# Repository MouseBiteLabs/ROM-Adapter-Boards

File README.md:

# ROM-Adapter-Boards
A collection of ROM adapter boards for different use cases

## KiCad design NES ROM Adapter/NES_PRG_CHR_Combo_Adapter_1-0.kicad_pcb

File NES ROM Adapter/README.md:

# NES ROM Adapter

Order at your own risk. Design is untested.

See instructions here: https://mousebitelabs.com/2020/06/17/eprom-to-nes-mask-rom-adapter-board/

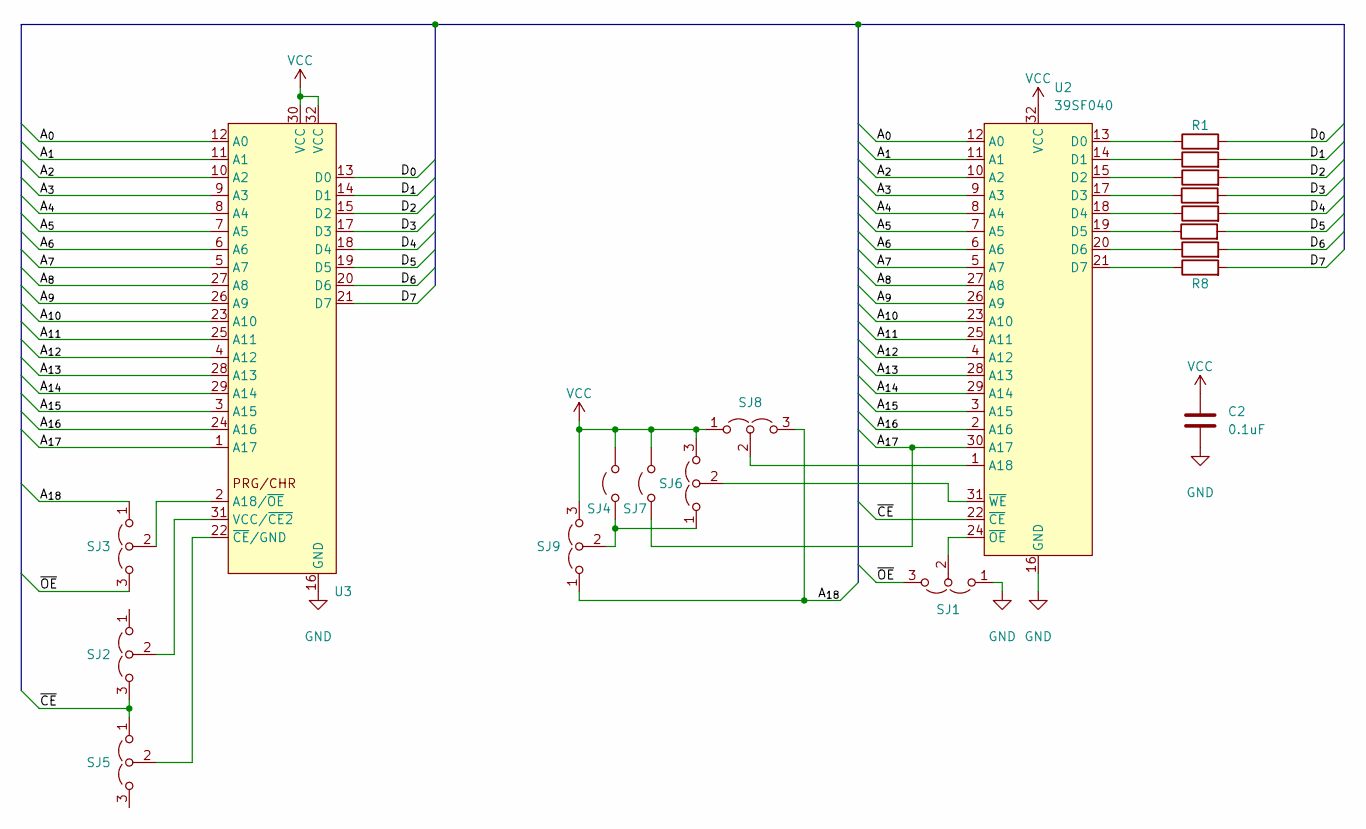
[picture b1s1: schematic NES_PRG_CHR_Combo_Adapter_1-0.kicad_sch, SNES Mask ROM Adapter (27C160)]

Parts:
C2: 0.1uF; THT_SMT_0803
R1, R2, R3, R4, R5, R6, R7, R8: R; R_0603_1608Metric_Boxed_SHORTED_DASHED
SJ1, SJ2, SJ3, SJ5, SJ6, SJ8, SJ9: Jumper_3_Open; SJ_2
SJ4, SJ7: Jumper_2_Open; SJ
U2, U3: 39SF040; DIP-32_W15.24mm

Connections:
/A_{0}: U2.12 (A0), U3.12 (A0); also elsewhere on the board
/A_{1}: U2.11 (A1), U3.11 (A1); also elsewhere on the board
/A_{2}: U2.10 (A2), U3.10 (A2); also elsewhere on the board
/A_{3}: U2.9 (A3), U3.9 (A3); also elsewhere on the board
/A_{4}: U2.8 (A4), U3.8 (A4); also elsewhere on the board
/A_{5}: U2.7 (A5), U3.7 (A5); also elsewhere on the board
/A_{6}: U2.6 (A6), U3.6 (A6); also elsewhere on the board
/A_{7}: U2.5 (A7), U3.5 (A7); also elsewhere on the board
/A_{8}: U2.27 (A8), U3.27 (A8); also elsewhere on the board
/A_{9}: U2.26 (A9), U3.26 (A9); also elsewhere on the board
/A_{10}: U2.23 (A10), U3.23 (A10); also elsewhere on the board
/A_{11}: U2.25 (A11), U3.25 (A11); also elsewhere on the board
/A_{12}: U2.4 (A12), U3.4 (A12); also elsewhere on the board
/A_{13}: U2.28 (A13), U3.28 (A13); also elsewhere on the board
/A_{14}: U2.29 (A14), U3.29 (A14); also elsewhere on the board
/A_{15}: U2.3 (A15), U3.3 (A15); also elsewhere on the board
/A_{16}: U2.2 (A16), U3.24 (A16); also elsewhere on the board
/A_{17}: SJ7.1 (A), U2.30 (A17), U3.1 (A17); also elsewhere on the board
/A_{18}: SJ3.1 (A), SJ8.3 (B), SJ9.1 (A)
/D_{0}: R1.2, U3.13 (D0)
/D_{1}: R2.2, U3.14 (D1)
/D_{2}: R3.2, U3.15 (D2)
/D_{3}: R4.2, U3.17 (D3)
/D_{4}: R5.2, U3.18 (D4)
/D_{5}: R6.2, U3.19 (D5)
/D_{6}: R7.2, U3.20 (D6)
/D_{7}: R8.2, U3.21 (D7)
/~CE: SJ2.3 (B), SJ5.1 (A), U2.22 (~CE); also elsewhere on the board
/~OE: SJ1.3 (B), SJ3.3 (B)
GND: C2.2, SJ1.1 (A), U2.16 (GND), U3.16 (GND); also elsewhere on the board
unnamed 30: SJ1.2 (C), U2.24 (~OE); also elsewhere on the board
unnamed: SJ2.2 (C), U3.31 (VCC/~CE2)
unnamed: SJ3.2 (C), U3.2 (A18/~OE)
unnamed: SJ4.1 (A), SJ6.1 (A), SJ9.2 (C)
unnamed: SJ5.2 (C), U3.22 (~CE/GND)
unnamed 35: SJ6.2 (C), U2.31 (~WE); also elsewhere on the board
unnamed 36: SJ8.2 (C), U2.1 (A18); also elsewhere on the board
unnamed 37: R1.1, U2.13 (D0); also elsewhere on the board
unnamed 38: R2.1, U2.14 (D1); also elsewhere on the board
unnamed 39: R3.1, U2.15 (D2); also elsewhere on the board
unnamed 40: R4.1, U2.17 (D3); also elsewhere on the board
unnamed 41: R5.1, U2.18 (D4); also elsewhere on the board
unnamed 42: R6.1, U2.19 (D5); also elsewhere on the board
unnamed 43: R7.1, U2.20 (D6); also elsewhere on the board
unnamed 44: R8.1, U2.21 (D7); also elsewhere on the board
VCC: C2.1, SJ4.2 (B), SJ6.3 (B), SJ7.2 (B), SJ8.1 (A), SJ9.3 (B), U2.32 (VCC), U3.30 (VCC), U3.32 (VCC); also elsewhere on the board

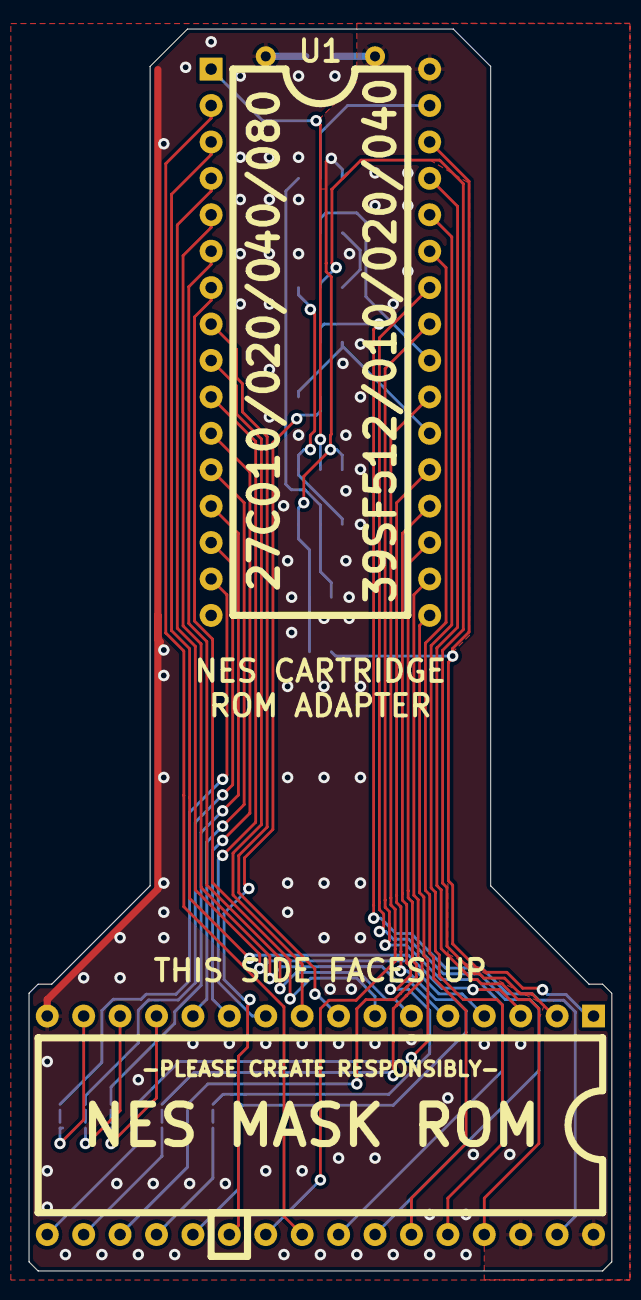
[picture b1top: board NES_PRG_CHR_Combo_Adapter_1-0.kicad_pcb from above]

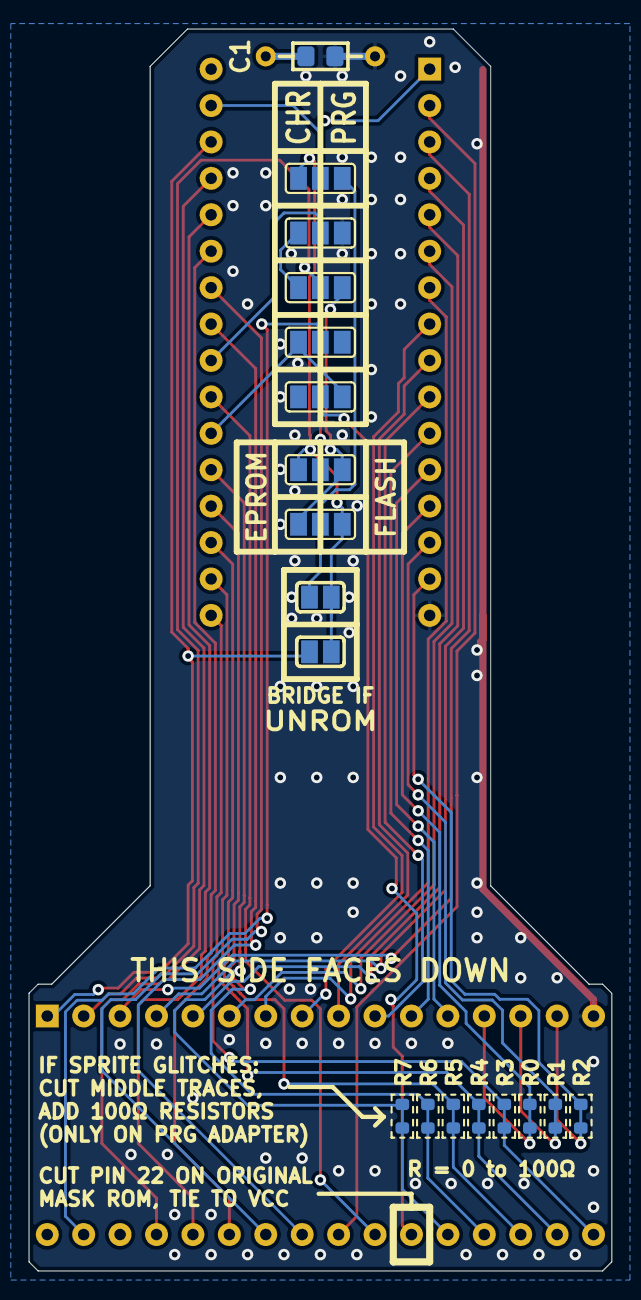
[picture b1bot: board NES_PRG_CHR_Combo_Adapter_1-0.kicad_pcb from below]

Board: 2 copper layers, 40.6 x 86.6 mm, 20 parts (18 on the bottom side), 46 nets.

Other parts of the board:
C1: 0.1uF; THT_SMT_0803
U1: 39SF040; DIP-32_W15.24mm

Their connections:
/A_{0}: U1.12 (A0); also elsewhere on the board
/A_{1}: U1.11 (A1); also elsewhere on the board
/A_{2}: U1.10 (A2); also elsewhere on the board
/A_{3}: U1.9 (A3); also elsewhere on the board
/A_{4}: U1.8 (A4); also elsewhere on the board
/A_{5}: U1.7 (A5); also elsewhere on the board
/A_{6}: U1.6 (A6); also elsewhere on the board
/A_{7}: U1.5 (A7); also elsewhere on the board
/A_{8}: U1.27 (A8); also elsewhere on the board
/A_{9}: U1.26 (A9); also elsewhere on the board
/A_{10}: U1.23 (A10); also elsewhere on the board
/A_{11}: U1.25 (A11); also elsewhere on the board
/A_{12}: U1.4 (A12); also elsewhere on the board
/A_{13}: U1.28 (A13); also elsewhere on the board
/A_{14}: U1.29 (A14); also elsewhere on the board
/A_{15}: U1.3 (A15); also elsewhere on the board
/A_{16}: U1.2 (A16); also elsewhere on the board
/A_{17}: U1.30 (A17); also elsewhere on the board
/~CE: U1.22 (~CE); also elsewhere on the board
GND: C1.2, U1.16 (GND); also elsewhere on the board
unnamed 30: U1.24 (~OE); also elsewhere on the board
unnamed 35: U1.31 (~WE); also elsewhere on the board
unnamed 36: U1.1 (A18); also elsewhere on the board
unnamed 37: U1.13 (D0); also elsewhere on the board
unnamed 38: U1.14 (D1); also elsewhere on the board
unnamed 39: U1.15 (D2); also elsewhere on the board
unnamed 40: U1.17 (D3); also elsewhere on the board
unnamed 41: U1.18 (D4); also elsewhere on the board
unnamed 42: U1.19 (D5); also elsewhere on the board
unnamed 43: U1.20 (D6); also elsewhere on the board
unnamed 44: U1.21 (D7); also elsewhere on the board
VCC: C1.1, U1.32 (VCC); also elsewhere on the board

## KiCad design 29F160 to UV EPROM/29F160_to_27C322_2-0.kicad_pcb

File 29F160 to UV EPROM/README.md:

# 29F160 to UV ERPOM Adapter

This board is used to recreate the old UV EPROMs 27C160 and 27C322 with brand new 29F160 EEPROMs. The UV EPROMs are typically only available to purchase used from places like AliExpress and eBay, and are known to occasionally arrive damaged or completely inoperable. The 29F160, however, is brand new NOR Flash manufactured by Alliance, for purchase at major electronics distributors.

<a href="https://mou.sr/3HIjb09">Here is a link to the component on Mouser.</a>

With one of these chips, you can make a replacement for the 27C160. With two, you can make a replacement for the 27C322. In fact, with the 29F160's /BYTE pin, you can even make an 8-bit bus version of the 27C322 which was only ever a feature of the 27C160.

*(In this image, the board is set up as a drop-in replacement for the 27C322)*

All gerbers and source files can be found in this repo, as this project is fully open source. Please read all instructions associated with this board before assembling.

## Board Characteristics and Order Information

The zipped folder contains all the gerber files for this board. You can generally choose whatever thickness you want, but I usually stick to at least 1.0mm. The surface finish can also be whatever you want, but I find ENIG easier to solder the small-pitch parts, personally. Also note that this is a four-layer board.

You can order this board on OSH Park, which is a great option if you only need a small quantity: [https://oshpark.com/shared_projects/efulo1p1](https://oshpark.com/shared_projects/efulo1p1)

Alternatively, you can use the zipped folder at any board fabricator you like. You may also buy the board from PCBWay using this link (NOT YET AVAILABLE) (disclosure: I receive 10% of the sale value to go towards future PCB orders of my own):

## Required Equipment

- You will need basic tools, like a soldering iron, hot plate, and/or hot air rework station. Drag soldering will be indispensible for this board.
- To program the 29F160 chips, you can use the <a href="https://xgecu.myshopify.com/products/xgecu-new-t48-tl866-3gprogrammer-v12-01-support-28000-ics-for-spi-nor-nand-flash-emmc-bga153-162-169-100-221-tsop-sop-plcc">T48 programmer</a> with the <a href="https://xgecu.myshopify.com/products/100-original-xgecu-adp_f48_ex-1-tsop48-special-adapter-for-nor-flash-only-use-on-t48-tl866-3g-programmer">TSOP48 adapter</a>.

## Programming Adapter

To make programming this board easier, I made this mouthful of an adapter board: the <a href="https://github.com/MouseBiteLabs/TSOP-NOR-Flash-Programming-Adapter-for-T48">TSOP NOR Flash Programming Adapter for T48</a>. It is untested (I haven't received them yet) but if it works, it will let you program both of the 29F160 chips on this breakout board without having to desolder them. You **will still need** the <a href="https://xgecu.myshopify.com/products/100-original-xgecu-adp_f48_ex-1-tsop48-special-adapter-for-nor-flash-only-use-on-t48-tl866-3g-programmer">TSOP48 adapter</a> because there's a proprietary EEPROM chip on there to communicate with the main programmer, but this makes it easier nonetheless.

Remember: this adapter is untested. I will update this repository after testing it.

## Board Configurations

Most of the configurations are self-explanatory or are described on the back of the board, but here's a breakdown.

### JP1 - 27C160 Mode Jumper

Bridge this solder pad if you are only using one 29F160 chip to replicate a 27C160. Note that this pad is located underneath U4 - meaning you **should not solder JP1 if you have U4 on the board**. U4 is required if you are using two 29F160 chips.

### R2 - The Byte Mode Resistor

This is a special three-way set of pads that sets the mode for the databus output. These sets of pads configures the 29F160's /BYTE pin, which tells the chip to output data in an 8-bit bus or a 16-bit bus. The 27C160 had the same pin feature (as pin 32) but the 27C322 was forced to output a 16-bit bus. The /BYTE pin(s) on U2 and U3 are connected to the middle-right pad. Solder a resistor between the top or bottom set of pads, or directly connect this pad to the left (labeled "P32") according to the following criteria:

- Solder the resistor R2 to the bottom footprint to force the data output to be a 16-bit bus. This is how the 27C322 operates natively, and one of the modes the 27C160 can operate in. If you are using two 29F160 chips, then soldering to the bottom pad will produce a drop-in replacement for the 27C322.
- Solder the resistor R2 to the top footprint to force the data output to be an 8-bit bus. The 27C160 can output an 8-bit bus, but the 27C322 was never able to!
- Directly solder to the left (or use a zero-ohm resistor) to replicate the 27C160 as a drop-in replacement. This is ONLY if you are replicating the 27C160, NOT the 27C322. Soldering to the left will connect the 29F160's /BYTE pin to the through-hole pin 32, which is where the 27C160's /BYTE pin is located. **Do not solder to the left if you are using two 29F160 chips! Pin 32 in this case is the top address pin for switching between the two chips, so it is already in use!**

NOTE: Instead of a solder blob for P32 connection, a zero-ohm resistor may be used instead. **Do not use any resistance value other than zero ohms for R2 if connecting to P32.**

## The /WE, /RP, and /BYTE Holes

R1 and R3 are pull-up resistors for /WE and /RP pins on the 29F160s. When in normal operation, these two pins need to be pulled to VCC to operate properly. The /BYTE pin, as described in the section above, needs to be pulled to VCC or GND through R2 (or controlled through pin 32 elsewhere on the main board this is connecting to). The /BYTE pin is connected to the hole on the right side, also labeled /BYTE.

These holes are for easy access for potential on-board programming (these are used by the aformentioned <a href="https://github.com/MouseBiteLabs/29F160-to-UV-EPROM-T48-Programming-Adapter/">29F160 to UV EPROM Programmming Adapter for the T48</a>). If you are using this adapter board on one of my cartridges, there may be support for in-circuit programming through these pins. See the repository for the cartridge in question for more information.

## Bill of Materials (BOM): 27C160 (16 Mbit or 2 MB)

| Reference | Value/Part Number | Package | Description      | Source                                           |
| --------- | ----------------- | ------- | ---------------- | ------------------------------------------------ |
| C1        | 0.1uF             | 0603    | Capacitor (MLCC) | [https://mou.sr/3ENc15O](https://mou.sr/3ENc15O) |
| R1        | 100k              | 0603    | Resistor         | https://mou.sr/49bgMnu                           |
| R2 (*NOTE)| 100k              | 0603    | Resistor         | https://mou.sr/49bgMnu                           |
| R2 (*NOTE)| Zero ohms         | 0603    | Resistor (Jumper)| https://mou.sr/4e1ABQg                           |
| R3        | 100k              | 0603    | Resistor         | https://mou.sr/49bgMnu                           |
| U2        | M29F160           | TSOP-48 | Flash EEPROM     | https://mou.sr/3HIjb09                           |

NOTE: As described above, R2 is zero ohms (or a short circuit) to the P32 pad if you are using this board as a drop-in replacement for 27C160.

## Bill of Materials (BOM): 27C322 (32 Mbit or 4 MB)

| Reference | Value/Part Number | Package  | Description      | Source                                           |
| --------- | ----------------- | -------- | ---------------- | ------------------------------------------------ |
| C1        | 0.1uF             | 0603     | Capacitor (MLCC) | [https://mou.sr/3ENc15O](https://mou.sr/3ENc15O) |
| C2        | 0.1uF             | 0603     | Capacitor (MLCC) | [https://mou.sr/3ENc15O](https://mou.sr/3ENc15O) |
| R1        | 100k              | 0603     | Resistor         | https://mou.sr/49bgMnu                           |
| R2        | 100k              | 0603     | Resistor         | https://mou.sr/49bgMnu                           |
| R3        | 100k              | 0603     | Resistor         | https://mou.sr/49bgMnu                           |
| U2        | M29F160           | TSOP-48  | Flash EEPROM     | https://mou.sr/3HIjb09                           |
| U3        | M29F160           | TSOP-48  | Flash EEPROM     | https://mou.sr/3HIjb09                           |
| U4        | 74HCT139          | TSSOP-16 | Decoder          | [https://mou.sr/4eqzppn](https://mou.sr/4eqzppn) |

## Revision History

### v2.0 - Release II

- Added /WE, /RP, and /BYTE holes for a stronger connection for external programming.
- Added R1, R2, and R3 pull-up resistors to remove the need for soldering/desoldering solder jumpers for switching between programming and operational modes.
  
### v1.2 - Release I

- Added /WE pad (JP3) for experimental on-board programming. Bridging JP3 tied the /WE pin to VCC for normal operation.

### v1.1 - Alpha

### v1.0 - Prototype

## License

<br />This work is licensed under a <a rel="license" href="http://creativecommons.org/licenses/by-sa/4.0/">Creative Commons Attribution-ShareAlike 4.0 International License</a>. You are able to copy and redistribute the material in any medium or format, as well as remix, transform, or build upon the material for any purpose (even commercial) - but you **must** give appropriate credit, provide a link to the license, and indicate if any changes were made.

©MouseBiteLabs 2025

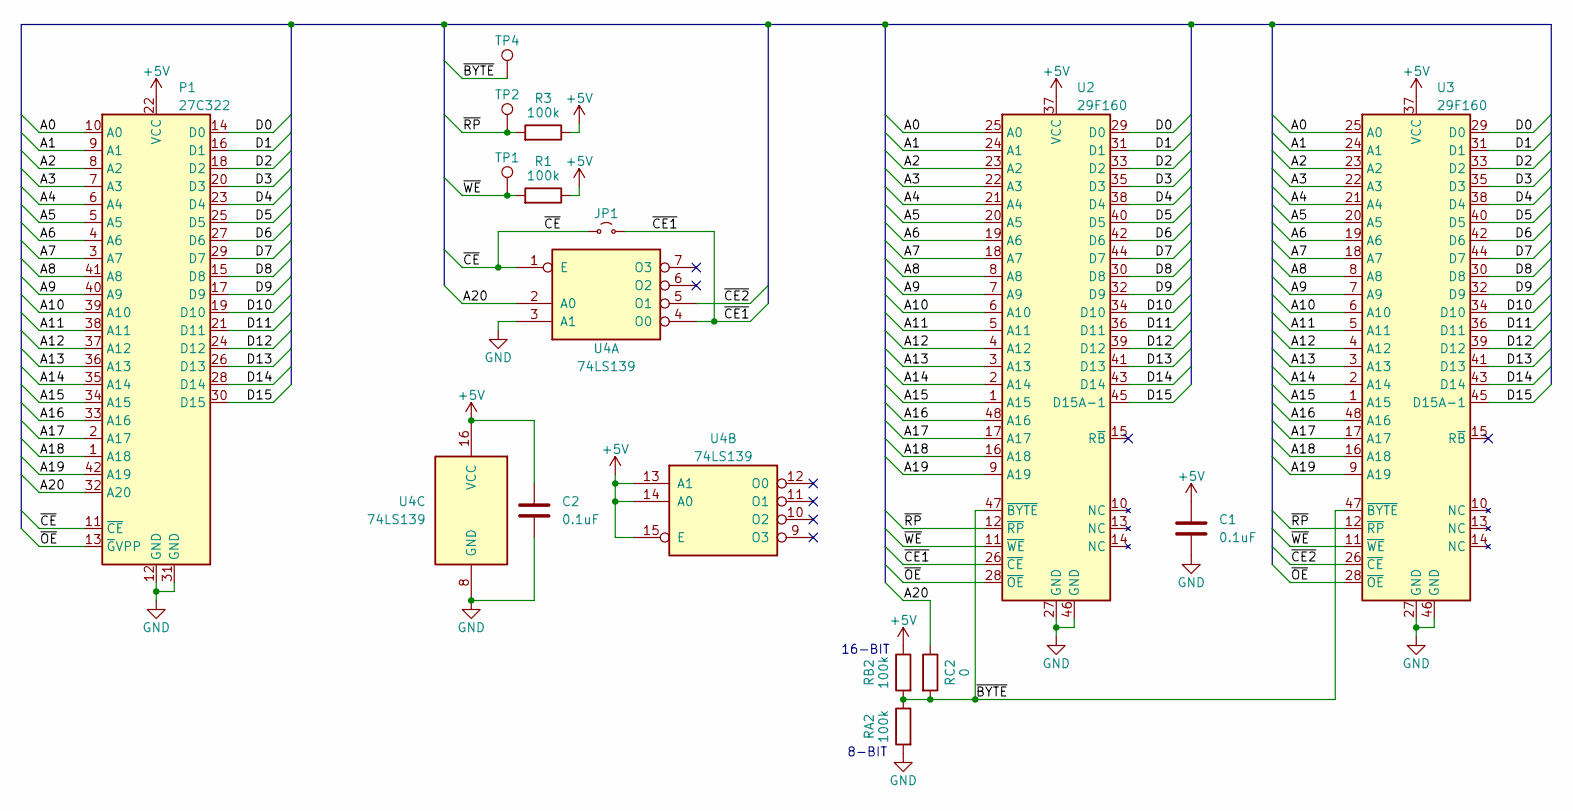
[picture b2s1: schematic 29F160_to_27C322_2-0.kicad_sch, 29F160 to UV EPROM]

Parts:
C1, C2: 0.1uF; C_0603_1608Metric
JP1: Jumper_2_Small_Open; SolderJumper-2_P1.3mm_Open_Pad1.0x1.5mm
P1: 27C322; DIP-42_W15.24mm
R1, R3: 100k; R_0603_1608Metric_Boxed
RA2: 100k; R_0603_1608Metric_Boxed
RB2: 100k; R_0603_1608Metric_Boxed
RC2: 0; R_0603_1608Metric_Boxed
TP1, TP2, TP4: TPB1,27; TestPoint_THTPad_D1.5mm_Drill0.7mm
U2, U3: 29F160; TSOP-I-48_18.4x12mm_P0.5mm
U4: 74LS139; TSSOP-16_4.4x5mm_P0.65mm

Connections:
+5V: C1.1, C2.1, P1.22 (VCC), R1.1, R3.1, RB2.1, U2.37 (VCC), U3.37 (VCC), U4.13 (A1), U4.14 (A0), U4.15 (E), U4.16 (VCC)
/A0: P1.10 (A0), U2.25 (A0), U3.25 (A0)
/A1: P1.9 (A1), U2.24 (A1), U3.24 (A1)
/A2: P1.8 (A2), U2.23 (A2), U3.23 (A2)
/A3: P1.7 (A3), U2.22 (A3), U3.22 (A3)
/A4: P1.6 (A4), U2.21 (A4), U3.21 (A4)
/A5: P1.5 (A5), U2.20 (A5), U3.20 (A5)
/A6: P1.4 (A6), U2.19 (A6), U3.19 (A6)
/A7: P1.3 (A7), U2.18 (A7), U3.18 (A7)
/A8: P1.41 (A8), U2.8 (A8), U3.8 (A8)
/A9: P1.40 (A9), U2.7 (A9), U3.7 (A9)
/A10: P1.39 (A10), U2.6 (A10), U3.6 (A10)
/A11: P1.38 (A11), U2.5 (A11), U3.5 (A11)
/A12: P1.37 (A12), U2.4 (A12), U3.4 (A12)
/A13: P1.36 (A13), U2.3 (A13), U3.3 (A13)
/A14: P1.35 (A14), U2.2 (A14), U3.2 (A14)
/A15: P1.34 (A15), U2.1 (A15), U3.1 (A15)
/A16: P1.33 (A16), U2.48 (A16), U3.48 (A16)
/A17: P1.2 (A17), U2.17 (A17), U3.17 (A17)
/A18: P1.1 (A18), U2.16 (A18), U3.16 (A18)
/A19: P1.42 (A19), U2.9 (A19), U3.9 (A19)
/A20: P1.32 (A20), RC2.1, U4.2 (A0)
/D0: P1.14 (D0), U2.29 (D0), U3.29 (D0)
/D1: P1.16 (D1), U2.31 (D1), U3.31 (D1)
/D2: P1.18 (D2), U2.33 (D2), U3.33 (D2)
/D3: P1.20 (D3), U2.35 (D3), U3.35 (D3)
/D4: P1.23 (D4), U2.38 (D4), U3.38 (D4)
/D5: P1.25 (D5), U2.40 (D5), U3.40 (D5)
/D6: P1.27 (D6), U2.42 (D6), U3.42 (D6)
/D7: P1.29 (D7), U2.44 (D7), U3.44 (D7)
/D8: P1.15 (D8), U2.30 (D8), U3.30 (D8)
/D9: P1.17 (D9), U2.32 (D9), U3.32 (D9)
/D10: P1.19 (D10), U2.34 (D10), U3.34 (D10)
/D11: P1.21 (D11), U2.36 (D11), U3.36 (D11)
/D12: P1.24 (D12), U2.39 (D12), U3.39 (D12)
/D13: P1.26 (D13), U2.41 (D13), U3.41 (D13)
/D14: P1.28 (D14), U2.43 (D14), U3.43 (D14)
/D15: P1.30 (D15), U2.45 (D15A-1), U3.45 (D15A-1)
/~BYTE: RA2.1, RB2.2, RC2.2, TP4.1, U2.47 (~BYTE), U3.47 (~BYTE)
/~CE1: JP1.2 (B), U2.26 (~CE), U4.4 (O0)
/~CE2: U3.26 (~CE), U4.5 (O1)
/~CE: JP1.1 (A), P1.11 (~CE), U4.1 (E)
/~OE: P1.13 (~GVPP), U2.28 (~OE), U3.28 (~OE)
/~RP: R3.2, TP2.1, U2.12 (~RP), U3.12 (~RP)
/~WE: R1.2, TP1.1, U2.11 (~WE), U3.11 (~WE)
GND: C1.2, C2.2, P1.12 (GND), P1.31 (GND), RA2.2, U2.27 (GND), U2.46 (GND), U3.27 (GND), U3.46 (GND), U4.3 (A1), U4.8 (GND)

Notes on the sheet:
16-BIT
8-BIT

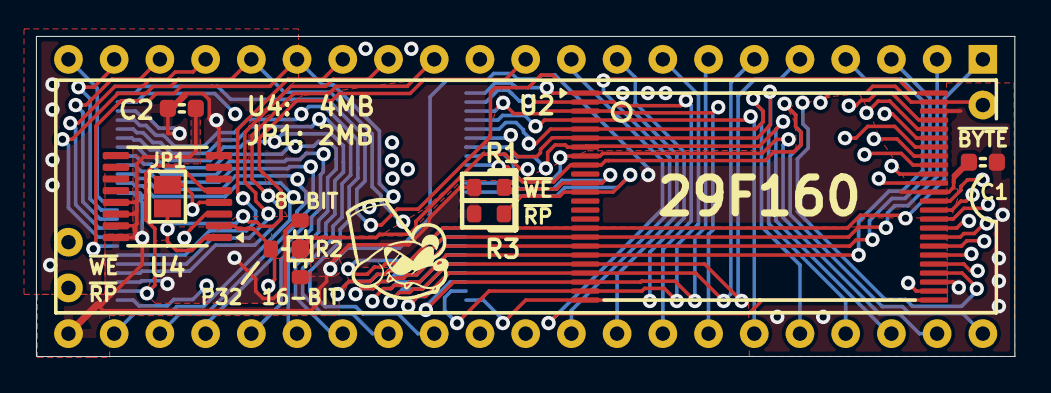
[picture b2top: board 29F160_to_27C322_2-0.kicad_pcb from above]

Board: 4 copper layers, 54.4 x 17.8 mm, 15 parts (1 on the bottom side), 46 nets.

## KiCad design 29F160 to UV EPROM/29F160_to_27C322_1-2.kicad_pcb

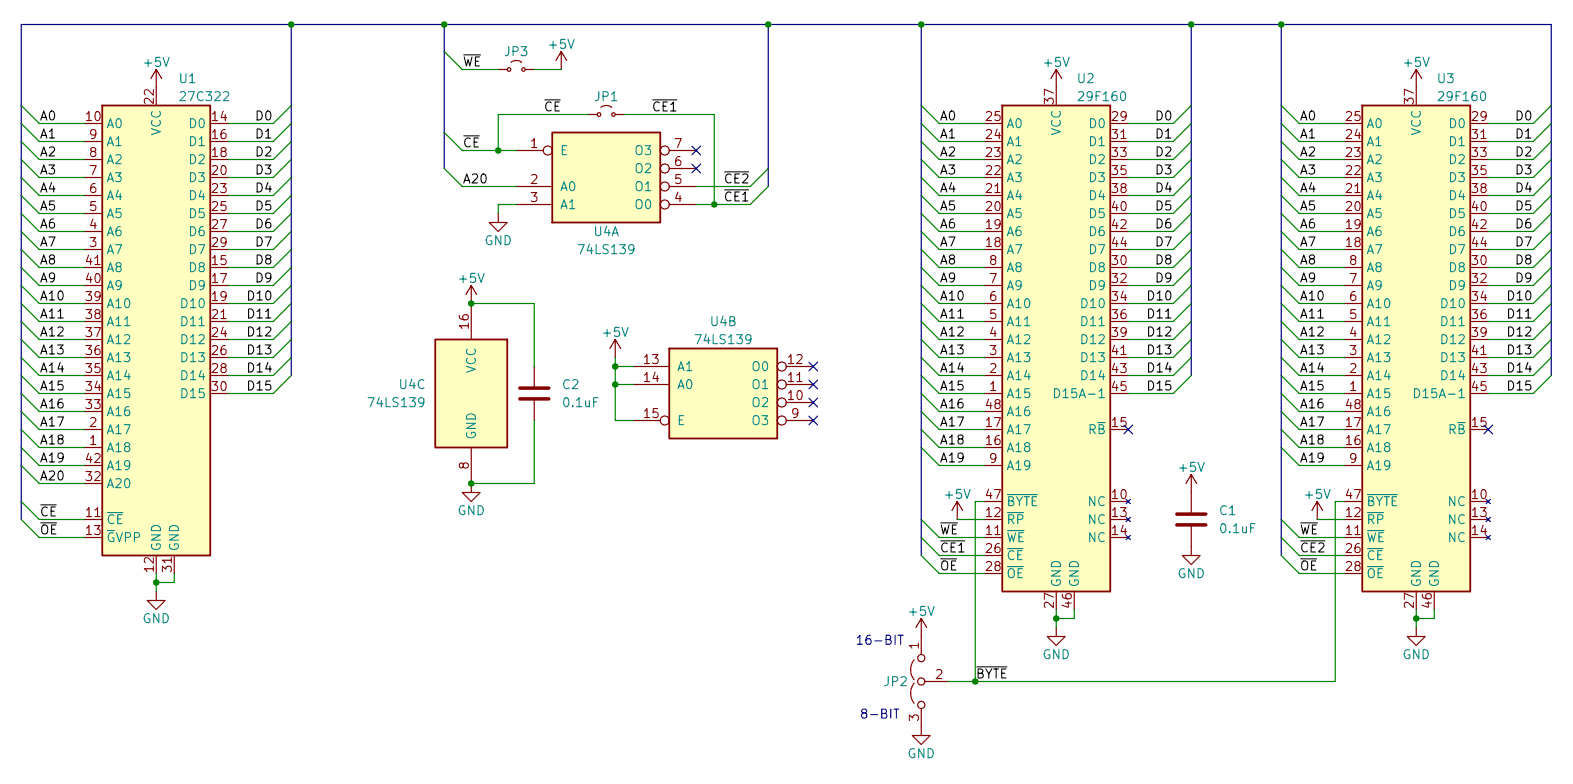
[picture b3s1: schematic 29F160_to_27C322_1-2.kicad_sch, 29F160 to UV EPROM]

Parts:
C1, C2: 0.1uF; C_0603_1608Metric
JP1, JP3: Jumper_2_Small_Open; SolderJumper-2_P1.3mm_Open_Pad1.0x1.5mm
JP2: Jumper_3_Open; SolderJumper-3_P1.3mm_Open_Pad1.0x1.5mm
U1: 27C322; DIP-42_W15.24mm
U2, U3: 29F160; TSOP-I-48_18.4x12mm_P0.5mm
U4: 74LS139; TSSOP-16_4.4x5mm_P0.65mm

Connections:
+5V: C1.1, C2.1, JP2.1 (A), JP3.2 (B), U1.22 (VCC), U2.12 (~RP), U2.37 (VCC), U3.12 (~RP), U3.37 (VCC), U4.13 (A1), U4.14 (A0), U4.15 (E), U4.16 (VCC)
/A0: U1.10 (A0), U2.25 (A0), U3.25 (A0)
/A1: U1.9 (A1), U2.24 (A1), U3.24 (A1)
/A2: U1.8 (A2), U2.23 (A2), U3.23 (A2)
/A3: U1.7 (A3), U2.22 (A3), U3.22 (A3)
/A4: U1.6 (A4), U2.21 (A4), U3.21 (A4)
/A5: U1.5 (A5), U2.20 (A5), U3.20 (A5)
/A6: U1.4 (A6), U2.19 (A6), U3.19 (A6)
/A7: U1.3 (A7), U2.18 (A7), U3.18 (A7)
/A8: U1.41 (A8), U2.8 (A8), U3.8 (A8)
/A9: U1.40 (A9), U2.7 (A9), U3.7 (A9)
/A10: U1.39 (A10), U2.6 (A10), U3.6 (A10)
/A11: U1.38 (A11), U2.5 (A11), U3.5 (A11)
/A12: U1.37 (A12), U2.4 (A12), U3.4 (A12)
/A13: U1.36 (A13), U2.3 (A13), U3.3 (A13)
/A14: U1.35 (A14), U2.2 (A14), U3.2 (A14)
/A15: U1.34 (A15), U2.1 (A15), U3.1 (A15)
/A16: U1.33 (A16), U2.48 (A16), U3.48 (A16)
/A17: U1.2 (A17), U2.17 (A17), U3.17 (A17)
/A18: U1.1 (A18), U2.16 (A18), U3.16 (A18)
/A19: U1.42 (A19), U2.9 (A19), U3.9 (A19)
/A20: U1.32 (A20), U4.2 (A0)
/D0: U1.14 (D0), U2.29 (D0), U3.29 (D0)
/D1: U1.16 (D1), U2.31 (D1), U3.31 (D1)
/D2: U1.18 (D2), U2.33 (D2), U3.33 (D2)
/D3: U1.20 (D3), U2.35 (D3), U3.35 (D3)
/D4: U1.23 (D4), U2.38 (D4), U3.38 (D4)
/D5: U1.25 (D5), U2.40 (D5), U3.40 (D5)
/D6: U1.27 (D6), U2.42 (D6), U3.42 (D6)
/D7: U1.29 (D7), U2.44 (D7), U3.44 (D7)
/D8: U1.15 (D8), U2.30 (D8), U3.30 (D8)
/D9: U1.17 (D9), U2.32 (D9), U3.32 (D9)
/D10: U1.19 (D10), U2.34 (D10), U3.34 (D10)
/D11: U1.21 (D11), U2.36 (D11), U3.36 (D11)
/D12: U1.24 (D12), U2.39 (D12), U3.39 (D12)
/D13: U1.26 (D13), U2.41 (D13), U3.41 (D13)
/D14: U1.28 (D14), U2.43 (D14), U3.43 (D14)
/D15: U1.30 (D15), U2.45 (D15A-1), U3.45 (D15A-1)
/~BYTE: JP2.2 (C), U2.47 (~BYTE), U3.47 (~BYTE)
/~CE1: JP1.2 (B), U2.26 (~CE), U4.4 (O0)
/~CE2: U3.26 (~CE), U4.5 (O1)
/~CE: JP1.1 (A), U1.11 (~CE), U4.1 (E)
/~OE: U1.13 (~GVPP), U2.28 (~OE), U3.28 (~OE)
/~WE: JP3.1 (A), U2.11 (~WE), U3.11 (~WE)
GND: C1.2, C2.2, JP2.3 (B), U1.12 (GND), U1.31 (GND), U2.27 (GND), U2.46 (GND), U3.27 (GND), U3.46 (GND), U4.3 (A1), U4.8 (GND)

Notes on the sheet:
16-BIT
8-BIT

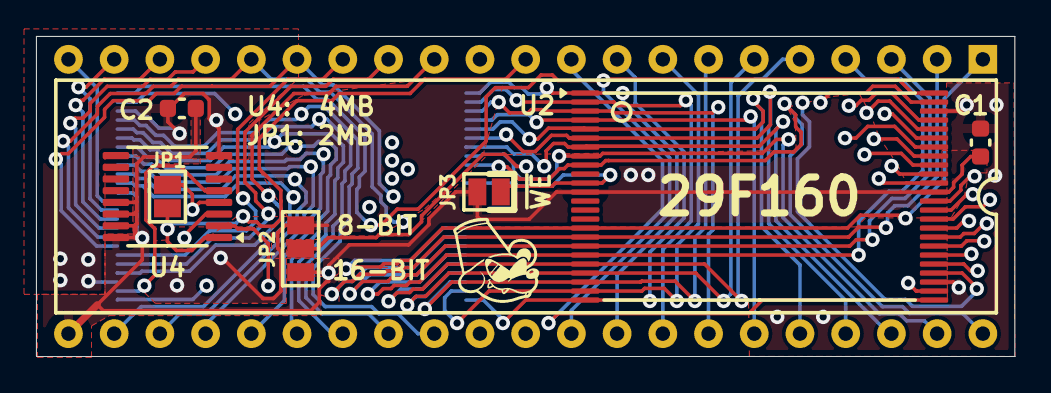
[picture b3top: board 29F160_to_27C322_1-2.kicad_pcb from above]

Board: 4 copper layers, 54.4 x 17.8 mm, 9 parts (1 on the bottom side), 45 nets.

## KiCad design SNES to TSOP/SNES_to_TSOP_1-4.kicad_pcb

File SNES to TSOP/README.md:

# SNES Mask ROM to TSOP

This board lets you use 29F016 or 29F032/29F033 TSOP EEPROMs to place in the SNES mask ROM socket on original SNES boards (or my [Basic UV boards](https://github.com/MouseBiteLabs/Super-Nintendo-Cartridges/tree/main/Basic%20UV)). You can also use two 29F016 chips (generally less expensive than the 29F033) to make a full 32 Mbit (4 MB) game.

All gerbers and source files can be found in this repo, as this project is fully open source. Please read all instructions associated with this board before assembling. **This design is intended for personal use only, not for modifying existing cartridges for commercial sale.** I really would rather you *not* use these adapter boards to repurpose old carts into rarer games or ROM hacks in order to sell them commercially.

## Board Characteristics and Order Information

The zipped folder contains all the gerber files for this board. You can generally choose whatever thickness you want, but I usually stick to at least 1.0mm. The surface finish can also be whatever you want, but I find ENIG easier to solder the small-pitch parts, personally. Also note that this is a four-layer board.

**I sell this blank circuit board on Etsy, so you don't have to buy a bunch of multiples if you don't want to.** (Click the banner!)

You can order this board on OSH Park, which is a great option if you only need a small quantity: https://oshpark.com/shared_projects/ZvoKSwja

Alternatively, you can use the zipped folder at any board fabricator you like. You may also buy the board from PCBWay using this link (NOT YET AVAILABLE) (disclosure: I receive 10% of the sale value to go towards future PCB orders of my own):

## Required Equipment

- You will need basic tools, like a soldering iron, hot plate, and/or hot air rework station. Drag soldering will be indispensible for this board.
- To program the 29F016 or 29F032/29F033 chips, you can use the <a href="https://xgecu.myshopify.com/products/xgecu-new-t48-tl866-3gprogrammer-v12-01-support-28000-ics-for-spi-nor-nand-flash-emmc-bga153-162-169-100-221-tsop-sop-plcc">T48 programmer</a> with the <a href="https://xgecu.myshopify.com/products/100-original-xgecu-adp_f48_ex-1-tsop48-special-adapter-for-nor-flash-only-use-on-t48-tl866-3g-programmer">TSOP48 adapter</a>.

## Programming Adapter

Coming soon.

## The /WE Pads

The right side of the pads marked /WE connects to the write enable pin of the TSOP(s). You can run a wire from the right pad to the /WR pin of your cartridge to use in a cart edge programmer (if the chips are supported). In this picture, the /WR pin from the cart edge (pin 54) is accessed via pin 27 of the SRAM.

If you are **not** using this capability, then simply bridge the two pads with solder.

## Board Configuration #1 - 16 Mbit (or 2 MB)

If your game is 16 Mbit or smaller, then use one 29F016 on the top TSOP footprint. Solder bridge the /CS pads within the 74'139 footprint. Please note the pin 1 indicator for the TSOP is on the bottom right corner.

### Bill of Materials (BOM): Configuration #1

| Reference | Value/Part Number | Package | Description      | Source                                           |
| --------- | ----------------- | ------- | ---------------- | ------------------------------------------------ |
| Top TSOP  | 29F016            | TSOP-48 | Flash EEPROM     | AliExpress, eBay                                 |

## Board Configuration #2 - 32 Mbit (or 4 MB) with the 29F032/29F033

If you want to make a game larger than 16 Mbit (up to 32 Mbit) you can use one 29F032/29F033 in place of the 29F016 described in the previous section. Again, bridge the /CS pads. Note that because this chip is (normally) 40-pins, you have to center it such that the outside pair of pins on each corner are empty, as shown below:

### Bill of Materials (BOM): Configuration #2

| Reference | Value/Part Number | Package | Description      | Source                                           |
| --------- | ----------------- | ------- | ---------------- | ------------------------------------------------ |
| Top TSOP  | 29F032/29F033     | TSOP-40 | Flash EEPROM     | AliExpress, eBay                                 |

## Board Configuration #3 - 32 Mbit (or 4 MB) with 2x 29F016

Finally, if you want to make a larger game with two 29F016 chips, you will need to populate both TSOP footprints, the 74'139 decoder, in addition to adding a solder bridge on the "PLAY" pads on the left of the board.

### Bill of Materials (BOM): Configuration #3

| Reference    | Value/Part Number | Package | Description      | Source                                           |
| ------------ | ----------------- | ------- | ---------------- | ------------------------------------------------ |
| Top TSOP     | 29F016            | TSOP-48 | Flash EEPROM     | AliExpress, eBay                                 |
| Bottom TSOP  | 29F016            | TSOP-48 | Flash EEPROM     | AliExpress, eBay                                 |
| 74'139       | 74HCT139          | SOIC-16 | Decoder          | [https://mou.sr/48Dk8As](https://mou.sr/48Dk8As) |

## "Patching" a Cartridge

Many people have asked if you can use these boards like [Voultar's Super Stacker](https://voultar.com/index.php?route=product/product&product_id=77), where you place these on the back of the original mask ROM without desoldering it. Many people use these for "patching" games with a translation or other hack. These boards *can* be used as such, but please keep in mind you're not actually patching the game, per se, you're disabling the original ROM chip and enabling a new one with the adapter board. You are not restricted to using a version of the game of the donor board you have, you can use any game that is compatible with the SNES board type.

If you want to do this - placing the board on the back of the original ROM chip without removing it - you can do it. It might be tricky, because the pins of the original chip are not very long. Keep these things in mind when installing:
- Make sure the adapter is still placed in the correct orientation. That means the top TSOP chip (and the decoder, if included) will be sandwiched between the original circuit board and the adapter circuit board.
- Make sure you have pin 1 lined up with pin 1 of the mask ROM.
- You still need to cut the /CE pin of the original ROM (pin 24) on the **TOP** of the board, and solder a wire from the cut pin to VCC (pin 36). This will disable the original chip.

## Revision History

### v1.4 - Re-release

- Ported from Eagle to KiCad

## License

<br />This work is licensed under a <a rel="license" href="http://creativecommons.org/licenses/by-sa/4.0/">Creative Commons Attribution-ShareAlike 4.0 International License</a>. You are able to copy and redistribute the material in any medium or format, as well as remix, transform, or build upon the material for any purpose (even commercial) - but you **must** give appropriate credit, provide a link to the license, and indicate if any changes were made.

©MouseBiteLabs 2025

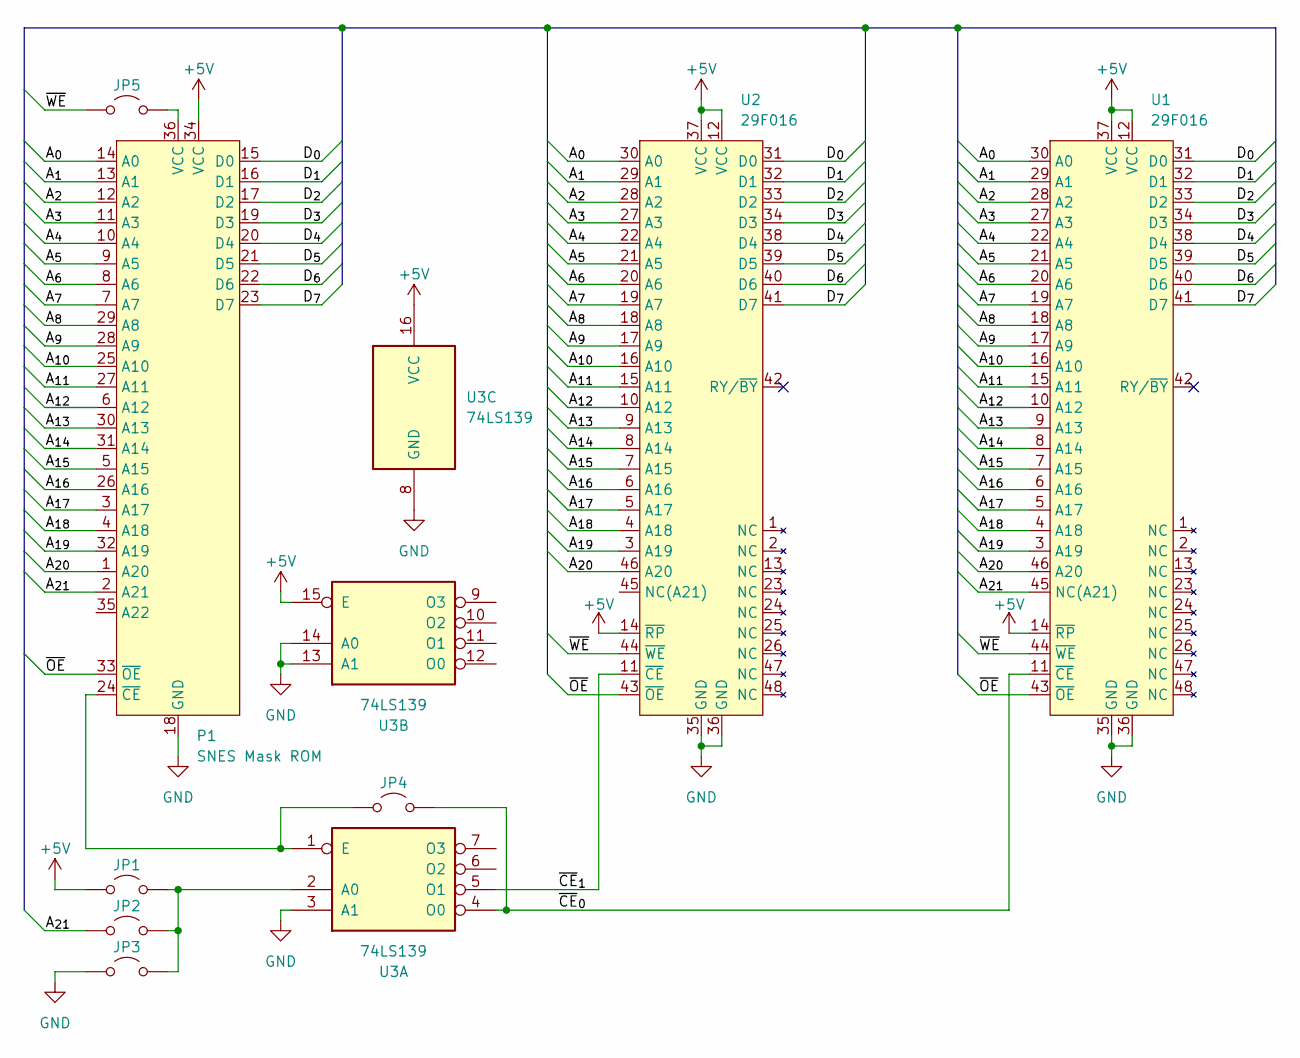
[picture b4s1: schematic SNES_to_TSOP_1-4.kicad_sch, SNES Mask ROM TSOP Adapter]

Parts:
JP1, JP2, JP3, JP4, JP5: Jumper_2_Open; SJ
P1: SNES Mask ROM; 36-PDIP
U1, U2: 29F016; 48-TSOP
U3: 74LS139; SO16_MOD

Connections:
+5V: JP1.1 (A), P1.34 (VCC), U1.12 (VCC), U1.14 (~RP), U1.37 (VCC), U2.12 (VCC), U2.14 (~RP), U2.37 (VCC), U3.15 (E), U3.16 (VCC)
/A_{0}: P1.14 (A0), U1.30 (A0), U2.30 (A0)
/A_{1}: P1.13 (A1), U1.29 (A1), U2.29 (A1)
/A_{2}: P1.12 (A2), U1.28 (A2), U2.28 (A2)
/A_{3}: P1.11 (A3), U1.27 (A3), U2.27 (A3)
/A_{4}: P1.10 (A4), U1.22 (A4), U2.22 (A4)
/A_{5}: P1.9 (A5), U1.21 (A5), U2.21 (A5)
/A_{6}: P1.8 (A6), U1.20 (A6), U2.20 (A6)
/A_{7}: P1.7 (A7), U1.19 (A7), U2.19 (A7)
/A_{8}: P1.29 (A8), U1.18 (A8), U2.18 (A8)
/A_{9}: P1.28 (A9), U1.17 (A9), U2.17 (A9)
/A_{10}: P1.25 (A10), U1.16 (A10), U2.16 (A10)
/A_{11}: P1.27 (A11), U1.15 (A11), U2.15 (A11)
/A_{12}: P1.6 (A12), U1.10 (A12), U2.10 (A12)
/A_{13}: P1.30 (A13), U1.9 (A13), U2.9 (A13)
/A_{14}: P1.31 (A14), U1.8 (A14), U2.8 (A14)
/A_{15}: P1.5 (A15), U1.7 (A15), U2.7 (A15)
/A_{16}: P1.26 (A16), U1.6 (A16), U2.6 (A16)
/A_{17}: P1.3 (A17), U1.5 (A17), U2.5 (A17)
/A_{18}: P1.4 (A18), U1.4 (A18), U2.4 (A18)
/A_{19}: P1.32 (A19), U1.3 (A19), U2.3 (A19)
/A_{20}: P1.1 (A20), U1.46 (A20), U2.46 (A20)
/A_{21}: JP2.1 (A), P1.2 (A21), U1.45 (NC(A21))
/D_{0}: P1.15 (D0), U1.31 (D0), U2.31 (D0)
/D_{1}: P1.16 (D1), U1.32 (D1), U2.32 (D1)
/D_{2}: P1.17 (D2), U1.33 (D2), U2.33 (D2)
/D_{3}: P1.19 (D3), U1.34 (D3), U2.34 (D3)
/D_{4}: P1.20 (D4), U1.38 (D4), U2.38 (D4)
/D_{5}: P1.21 (D5), U1.39 (D5), U2.39 (D5)
/D_{6}: P1.22 (D6), U1.40 (D6), U2.40 (D6)
/D_{7}: P1.23 (D7), U1.41 (D7), U2.41 (D7)
/~CE_{0}: JP4.2 (B), U1.11 (~CE), U3.4 (O0)
/~CE_{1}: U2.11 (~CE), U3.5 (O1)
/~OE: P1.33 (~OE), U1.43 (~OE), U2.43 (~OE)
/~WE: JP5.1 (A), U1.44 (~WE), U2.44 (~WE)
GND: JP3.1 (A), P1.18 (GND), U1.35 (GND), U1.36 (GND), U2.35 (GND), U2.36 (GND), U3.3 (A1), U3.8 (GND), U3.13 (A1), U3.14 (A0)
unnamed: JP1.2 (B), JP2.2 (B), JP3.2 (B), U3.2 (A0)
unnamed: JP4.1 (A), P1.24 (~CE), U3.1 (E)
unnamed: JP5.2 (B), P1.36 (VCC)

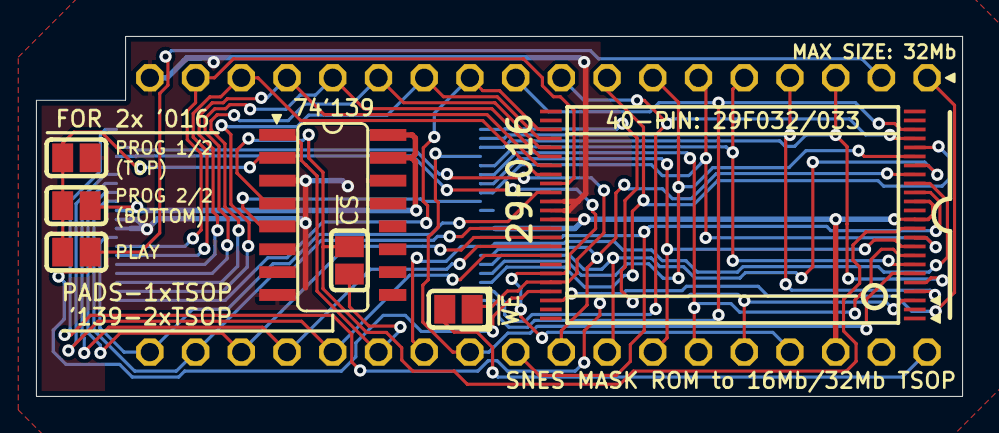
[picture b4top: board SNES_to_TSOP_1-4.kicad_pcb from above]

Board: 2 copper layers, 51.4 x 20.0 mm, 9 parts (1 on the bottom side), 39 nets.

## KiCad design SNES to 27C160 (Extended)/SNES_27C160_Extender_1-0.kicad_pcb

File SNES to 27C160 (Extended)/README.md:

# SNES Mask ROM to 27C160 (Extended)

**Design is intended for personal use only, not for modifying existing cartridges for commercial sale.** I really would rather you *not* use these adapter boards to repurpose old carts into rarer games or ROM hacks in order to sell them commercially. Use a brand new cart circuit board instead! I have plenty to choose from :)

Instructions: https://mousebitelabs.com/2020/01/28/27c322-27c160-to-snes-mask-rom-extended-adapter-board/

OSH Park: https://oshpark.com/shared_projects/zfUtl7pN (sorry it's expensive but tariffs ain't making these any cheaper from overseas)

## License

<br />This work is licensed under a <a rel="license" href="http://creativecommons.org/licenses/by-sa/4.0/">Creative Commons Attribution-ShareAlike 4.0 International License</a>. You are able to copy and redistribute the material in any medium or format, as well as remix, transform, or build upon the material for any purpose (even commercial) - but you **must** give appropriate credit, provide a link to the license, and indicate if any changes were made.

©MouseBiteLabs 2025

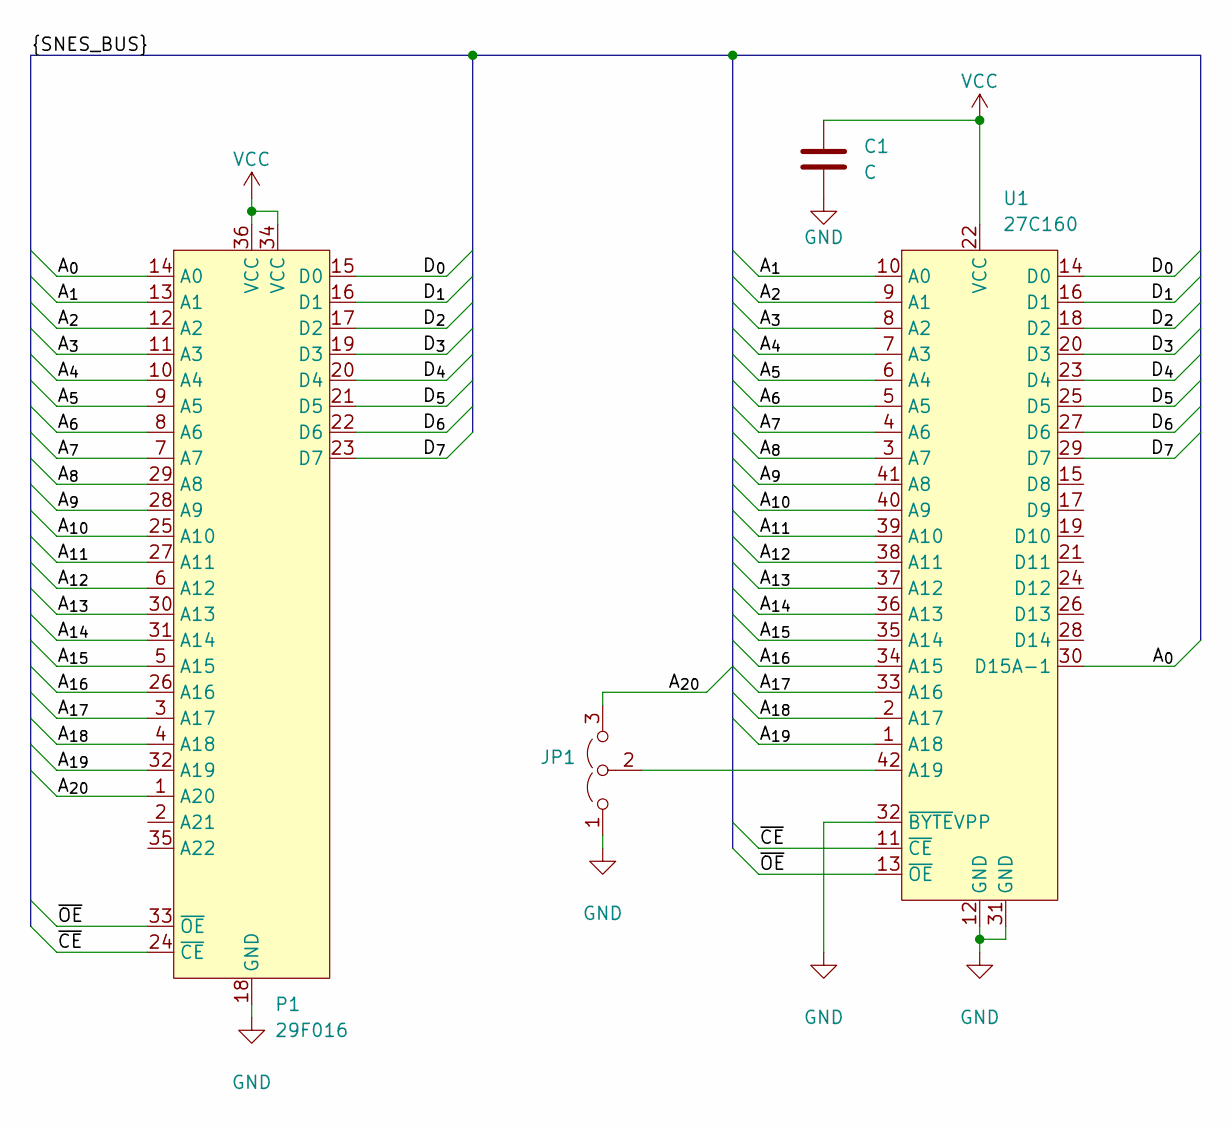
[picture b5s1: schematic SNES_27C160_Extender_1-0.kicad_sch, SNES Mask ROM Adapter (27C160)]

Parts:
C1: C; C_THT
JP1: Jumper_3_Open; SJ_2
P1: 29F016; 36-PDIP
U1: 27C160; PDIP_42_Offset_Pads

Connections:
/A_{0}: P1.14 (A0), U1.30 (D15A-1)
/A_{1}: P1.13 (A1), U1.10 (A0)
/A_{2}: P1.12 (A2), U1.9 (A1)
/A_{3}: P1.11 (A3), U1.8 (A2)
/A_{4}: P1.10 (A4), U1.7 (A3)
/A_{5}: P1.9 (A5), U1.6 (A4)
/A_{6}: P1.8 (A6), U1.5 (A5)
/A_{7}: P1.7 (A7), U1.4 (A6)
/A_{8}: P1.29 (A8), U1.3 (A7)
/A_{9}: P1.28 (A9), U1.41 (A8)
/A_{10}: P1.25 (A10), U1.40 (A9)
/A_{11}: P1.27 (A11), U1.39 (A10)
/A_{12}: P1.6 (A12), U1.38 (A11)
/A_{13}: P1.30 (A13), U1.37 (A12)
/A_{14}: P1.31 (A14), U1.36 (A13)
/A_{15}: P1.5 (A15), U1.35 (A14)
/A_{16}: P1.26 (A16), U1.34 (A15)
/A_{17}: P1.3 (A17), U1.33 (A16)
/A_{18}: P1.4 (A18), U1.2 (A17)
/A_{19}: P1.32 (A19), U1.1 (A18)
/A_{20}: JP1.3 (B), P1.1 (A20)
/D_{0}: P1.15 (D0), U1.14 (D0)
/D_{1}: P1.16 (D1), U1.16 (D1)
/D_{2}: P1.17 (D2), U1.18 (D2)
/D_{3}: P1.19 (D3), U1.20 (D3)
/D_{4}: P1.20 (D4), U1.23 (D4)
/D_{5}: P1.21 (D5), U1.25 (D5)
/D_{6}: P1.22 (D6), U1.27 (D6)
/D_{7}: P1.23 (D7), U1.29 (D7)
/~CE: P1.24 (~CE), U1.11 (~CE)
/~OE: P1.33 (~OE), U1.13 (~OE)
GND: C1.2, JP1.1 (A), P1.18 (GND), U1.12 (GND), U1.31 (GND), U1.32 (~BYTEVPP)
unnamed: JP1.2 (C), U1.42 (A19)
VCC: C1.1, P1.34 (VCC), P1.36 (VCC), U1.22 (VCC)
